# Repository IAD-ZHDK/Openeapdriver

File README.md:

# Open EAP driver
A driver and sequencer for prototyping with Dielectric Elastomers (Electroactive Polymers or EAP).

The device has both a push button activation control for EAP and an onboard sequencer for cyclic testing and creative purposes. For interactive work or for working in combination with other devices such as Arduino, the driver can be operated with a 5 volt signal from an external source. The device has an internal lipo battery with usb charging, and “hotswap” power management for uninterrupted usage during charging. The unit is based on the A50 high voltage converter from www.xppower.com (formerly EMCO). 

The Device Features:
* Internal Lipo Battery
* Rechargable over USB 
* Built in sequencer 
* Digital inputs for control with arduino 
* Push button control
* Indicator LEDS for battery charging

The maximum 5000 volt output of this device may result in electric shock if used incorrectly. Use at your own risk!

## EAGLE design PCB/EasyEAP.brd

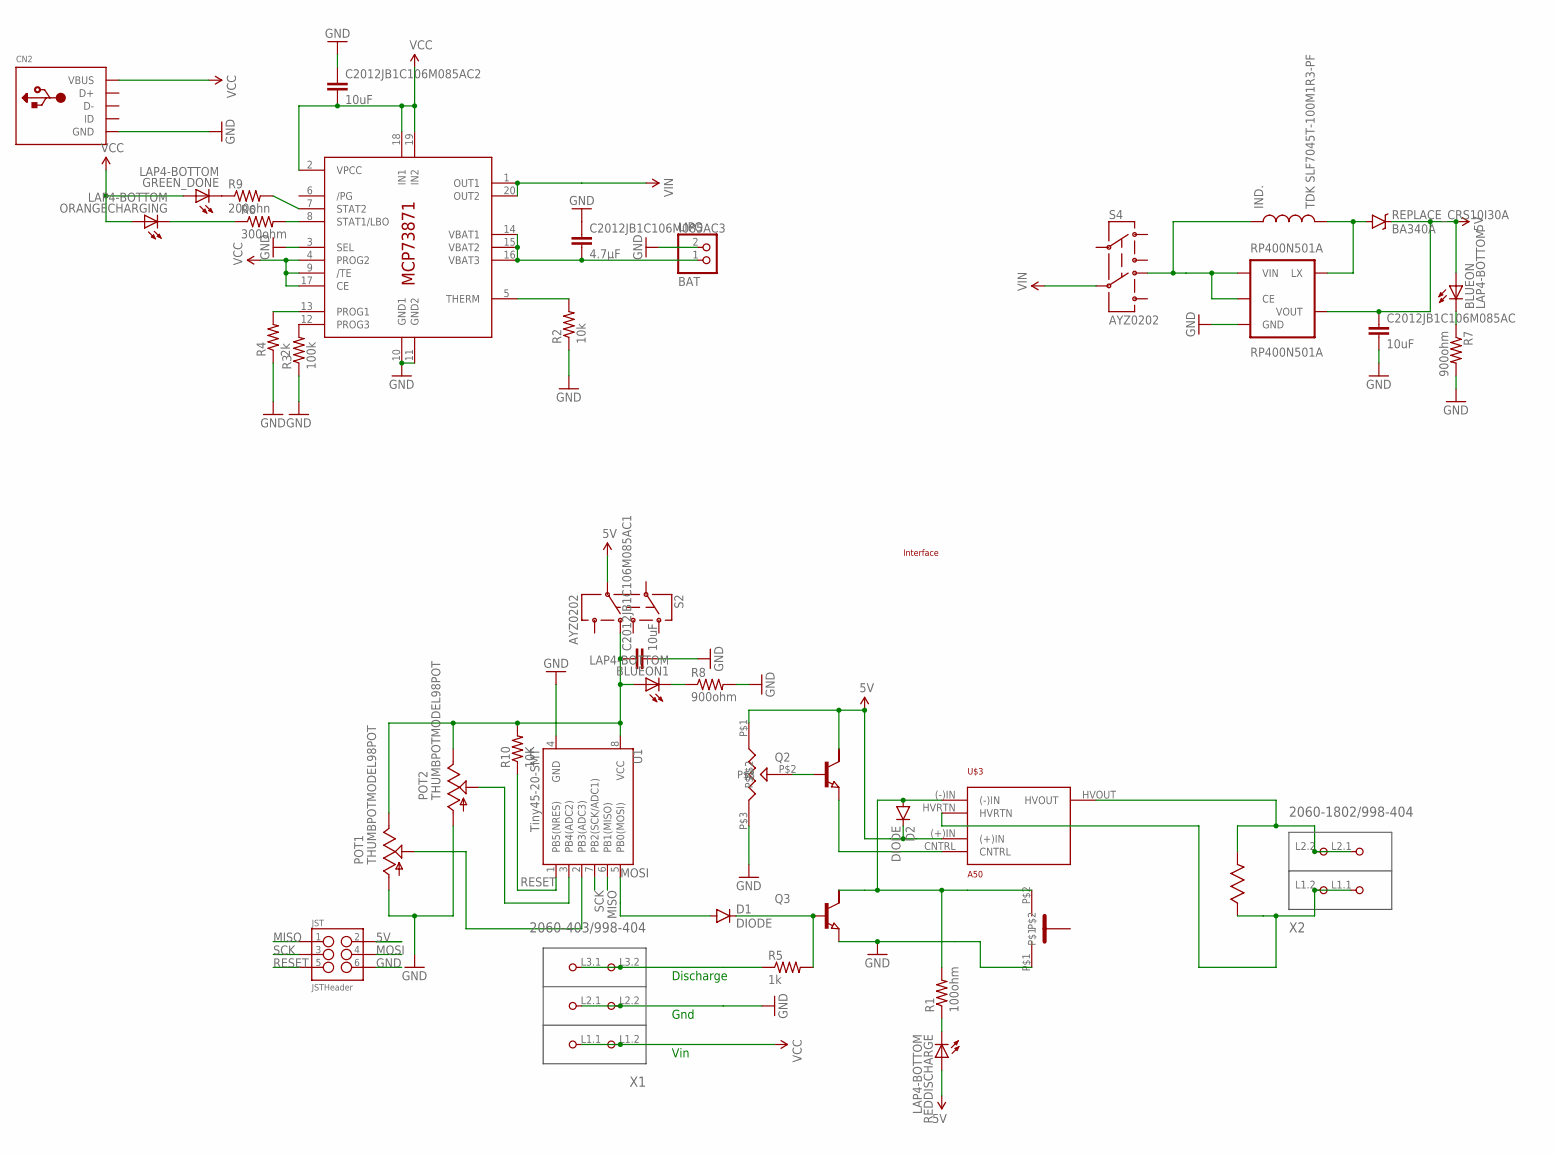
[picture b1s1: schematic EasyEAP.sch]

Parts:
BLUEON, BLUEON1: LAP4-BOTTOM; P47F-BOTTOM
C2012JB1C106M085AC, C2012JB1C106M085AC1, C2012JB1C106M085AC2: 10uF; 1210
C2012JB1C106M085AC3: 4.7μF; 1210
CN2: USBMINIB; USB-MINIB
D1, D2: DIODE; SMA-DIODE_ALT
GREEN_DONE: LAP4-BOTTOM; P47F-BOTTOM
IC1: MCP73871; QFN20
IND.: TDK SLF7045T-100M1R3-PF; B82462G
JST: JSTHeader; 2X3_SMD
LIPO: BAT; JST-PH-2-SMT-RA
ORANGECHARGING: LAP4-BOTTOM; P47F-BOTTOM
POT1, POT2: THUMBPOTMODEL98POT; THUMBWHEEL
Q2, Q3: NPN-TRANSISTIOR-2COLSOT89; SOT89
R1: 100ohm; 1206
R2: 10k; 1206
R3: 100k; 1206
R4: 2k; 1206
R5: 1k; 1206
R6: 300ohm; 1206
R7, R8: 900ohm; 1206
R9: 200ohn; 1206
R10: 10K; 1206
REDDISCHARGE: LAP4-BOTTOM; P47F-BOTTOM
REPLACE_CRS10I30A: BA340A; SMA-DIODE
RP400N501A: RP400N501A; SOT23-5
S2, S4: AYZ0202
U1: Tiny45-20-SMT; SO08-EIAJ
U$2: 4020SMD
U$3: A50
U$8: VISHAY
U$9: GRAYHILLPUSHBUTTON; GRAYHILLSERIES30
U$10: INTERFACE_EAP
X1: 2060-403/998-404; P-2060-403/998-404
X2: 2060-1802/998-404; P-2060-1802/998-404

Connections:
5V: BLUEON.A, C2012JB1C106M085AC.1, D2.C, JST.2, Q2.2 (C), REDDISCHARGE.A, REPLACE_CRS10I30A.C, RP400N501A.4 (VOUT), S2.5, U$3.(+)IN, U$8.P$1
5VSEQUENCE: BLUEON1.A, C2012JB1C106M085AC1.1, POT1.3 (E), POT2.3 (E), R10.2, S2.6 (4), U1.8 (VCC)
15K: POT1.2 (S), U1.2 (PB3(ADC3))
DISCHARGE: R5.1, X1.L3.1 (P3.1), X1.L3.2 (P3.2)
GND: C2012JB1C106M085AC.2, C2012JB1C106M085AC1.2, C2012JB1C106M085AC2.1, C2012JB1C106M085AC3.1, CN2.GND, IC1.3 (SEL), IC1.10 (GND1), IC1.11 (GND2), JST.6, LIPO.2 (1), POT1.1 (A), POT2.1 (A), Q3.3 (E), R2.1, R3.1, R4.1, R7.2, R8.2, RP400N501A.2 (GND), U1.4 (GND), U$8.P$3, U$9.P$1, X1.L2.1 (P2.1), X1.L2.2 (P2.2)
HVIN: U$2.P$1, U$3.HVRTN, X2.L1.1 (P1.1), X2.L1.2 (P1.2)
HVOUT: U$2.P$2, U$3.HVOUT, X2.L2.1 (P2.1), X2.L2.2 (P2.2)
MISO: JST.1, U1.6 (PB1(MISO))
MOSI: D1.A, JST.4, U1.5 (PB0(MOSI))
unnamed: IND..P$2 (2), REPLACE_CRS10I30A.A, RP400N501A.5 (LX)
unnamed: D1.C, Q3.1 (B), R5.2
unnamed: BLUEON.C, R7.1
unnamed: D2.A, Q3.2 (C), R1.2, U$3.(-)IN, U$9.P$2
unnamed: R1.1, REDDISCHARGE.C
unnamed: BLUEON1.C, R8.1
unnamed: C2012JB1C106M085AC3.2, IC1.14 (VBAT1), IC1.15 (VBAT2), IC1.16 (VBAT3), LIPO.1 (2)
unnamed: Q2.3 (E), U$3.CNTRL
unnamed: IC1.5 (THERM), R2.2
unnamed: IC1.12 (PROG3), R3.2
unnamed: Q2.1 (B), U$8.P$2
unnamed: IC1.13 (PROG1), R4.2
unnamed: POT2.2 (S), U1.3 (PB4(ADC2))
unnamed: IC1.8 (STAT1/LBO), R6.2
unnamed: ORANGECHARGING.C, R6.1
unnamed: IND..P$1 (1), RP400N501A.1 (CE), RP400N501A.3 (VIN), S4.6 (4)
unnamed: GREEN_DONE.C, R9.1
unnamed: IC1.7 (STAT2), R9.2
RESET: JST.5, R10.1, U1.1 (PB5(NRES))
SCK: JST.3, U1.7 (PB2(SCK/ADC1))
VCC: C2012JB1C106M085AC2.2, CN2.VBUS, GREEN_DONE.A, IC1.2 (VPCC), IC1.4 (PROG2), IC1.9 (/TE), IC1.17 (CE), IC1.18 (IN1), IC1.19 (IN2), ORANGECHARGING.A, X1.L1.1 (P1.1), X1.L1.2 (P1.2)
VIN: IC1.1 (OUT1), IC1.20 (OUT2), S4.5

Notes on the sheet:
Vin
Gnd
Discharge

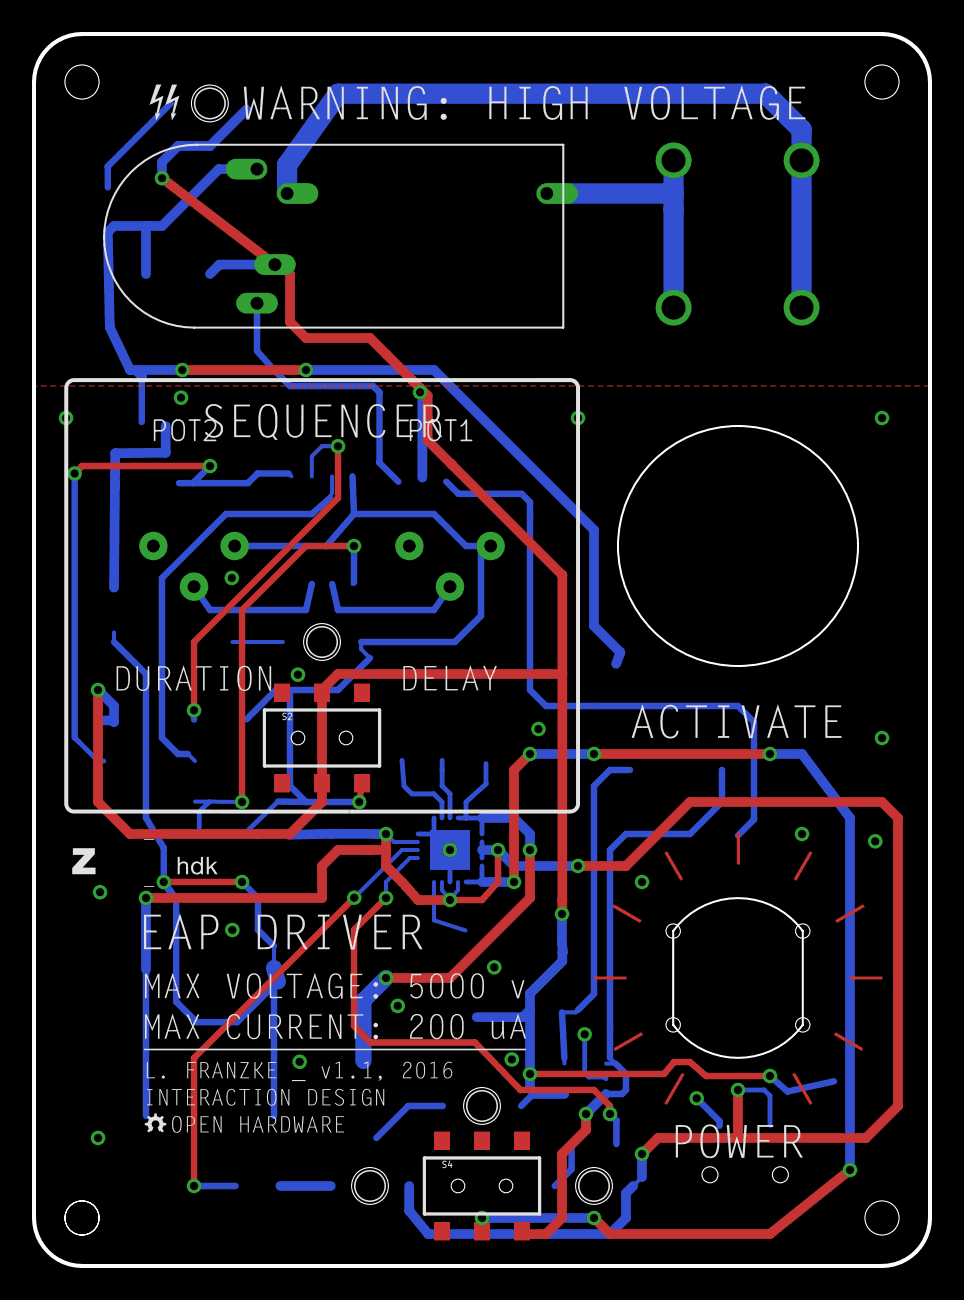
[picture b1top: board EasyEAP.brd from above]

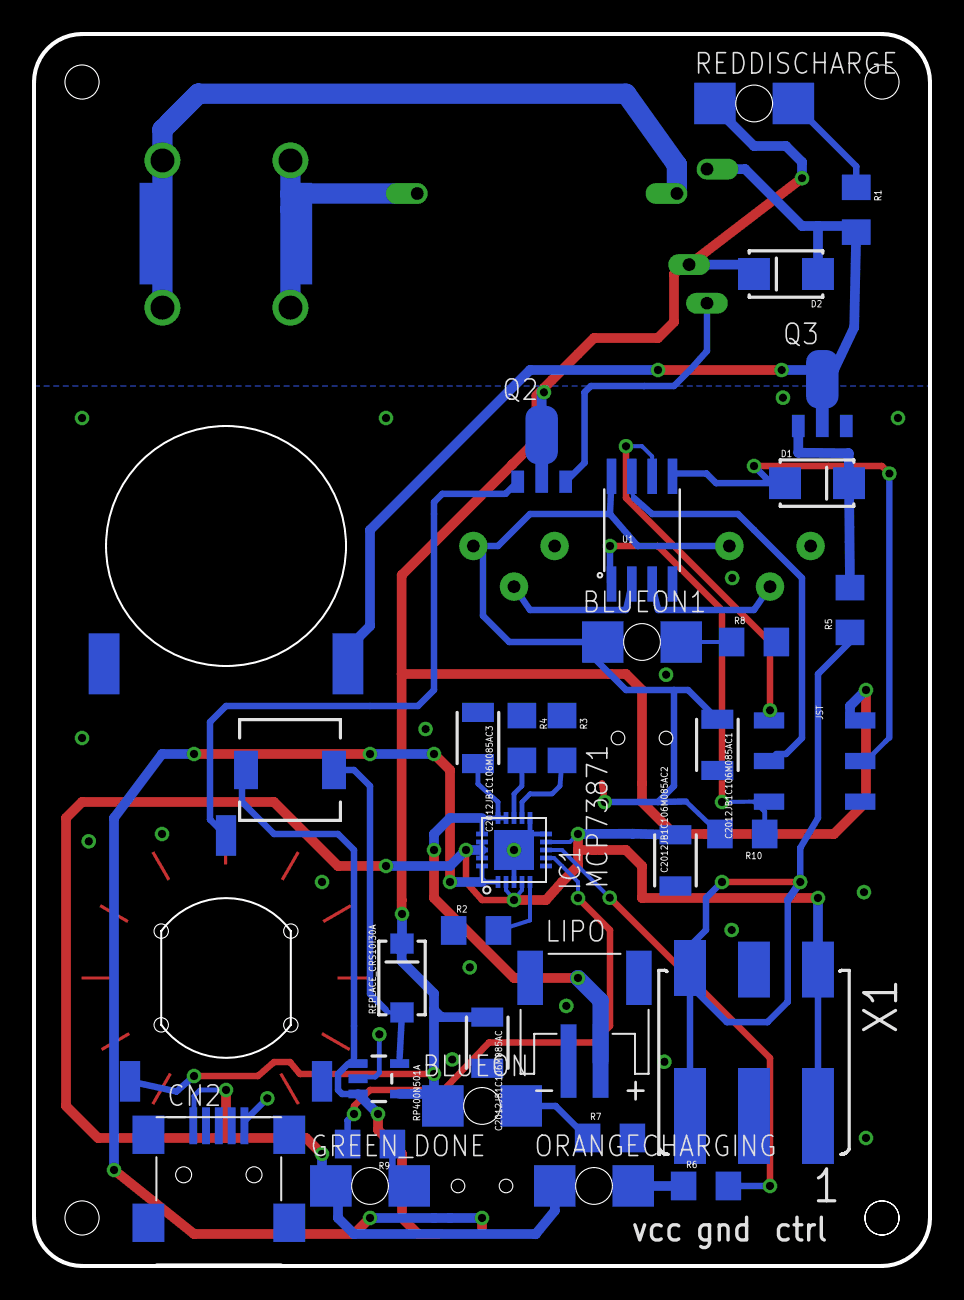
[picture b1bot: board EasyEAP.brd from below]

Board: 2 copper layers, 56.0 x 77.0 mm, 43 parts (33 on the bottom side), 31 nets.

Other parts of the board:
U$6: WARNING

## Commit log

2018-07-05 New Image
2018-07-05 Reduced Resolution Image
2018-07-05 Image Added
2018-07-05 Image Fixed
2018-07-05 Fixed Image

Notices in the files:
parts and their libraries:
SparkFun-DigitalIC: Licensing: CC v3.0 Share-Alike You are welcome to use this library for commercial purposes.
SparkFun-Connectors: Licensing: Creative Commons ShareAlike 4.0 International - https://creativecommons.org/licenses/by-sa/4.0
